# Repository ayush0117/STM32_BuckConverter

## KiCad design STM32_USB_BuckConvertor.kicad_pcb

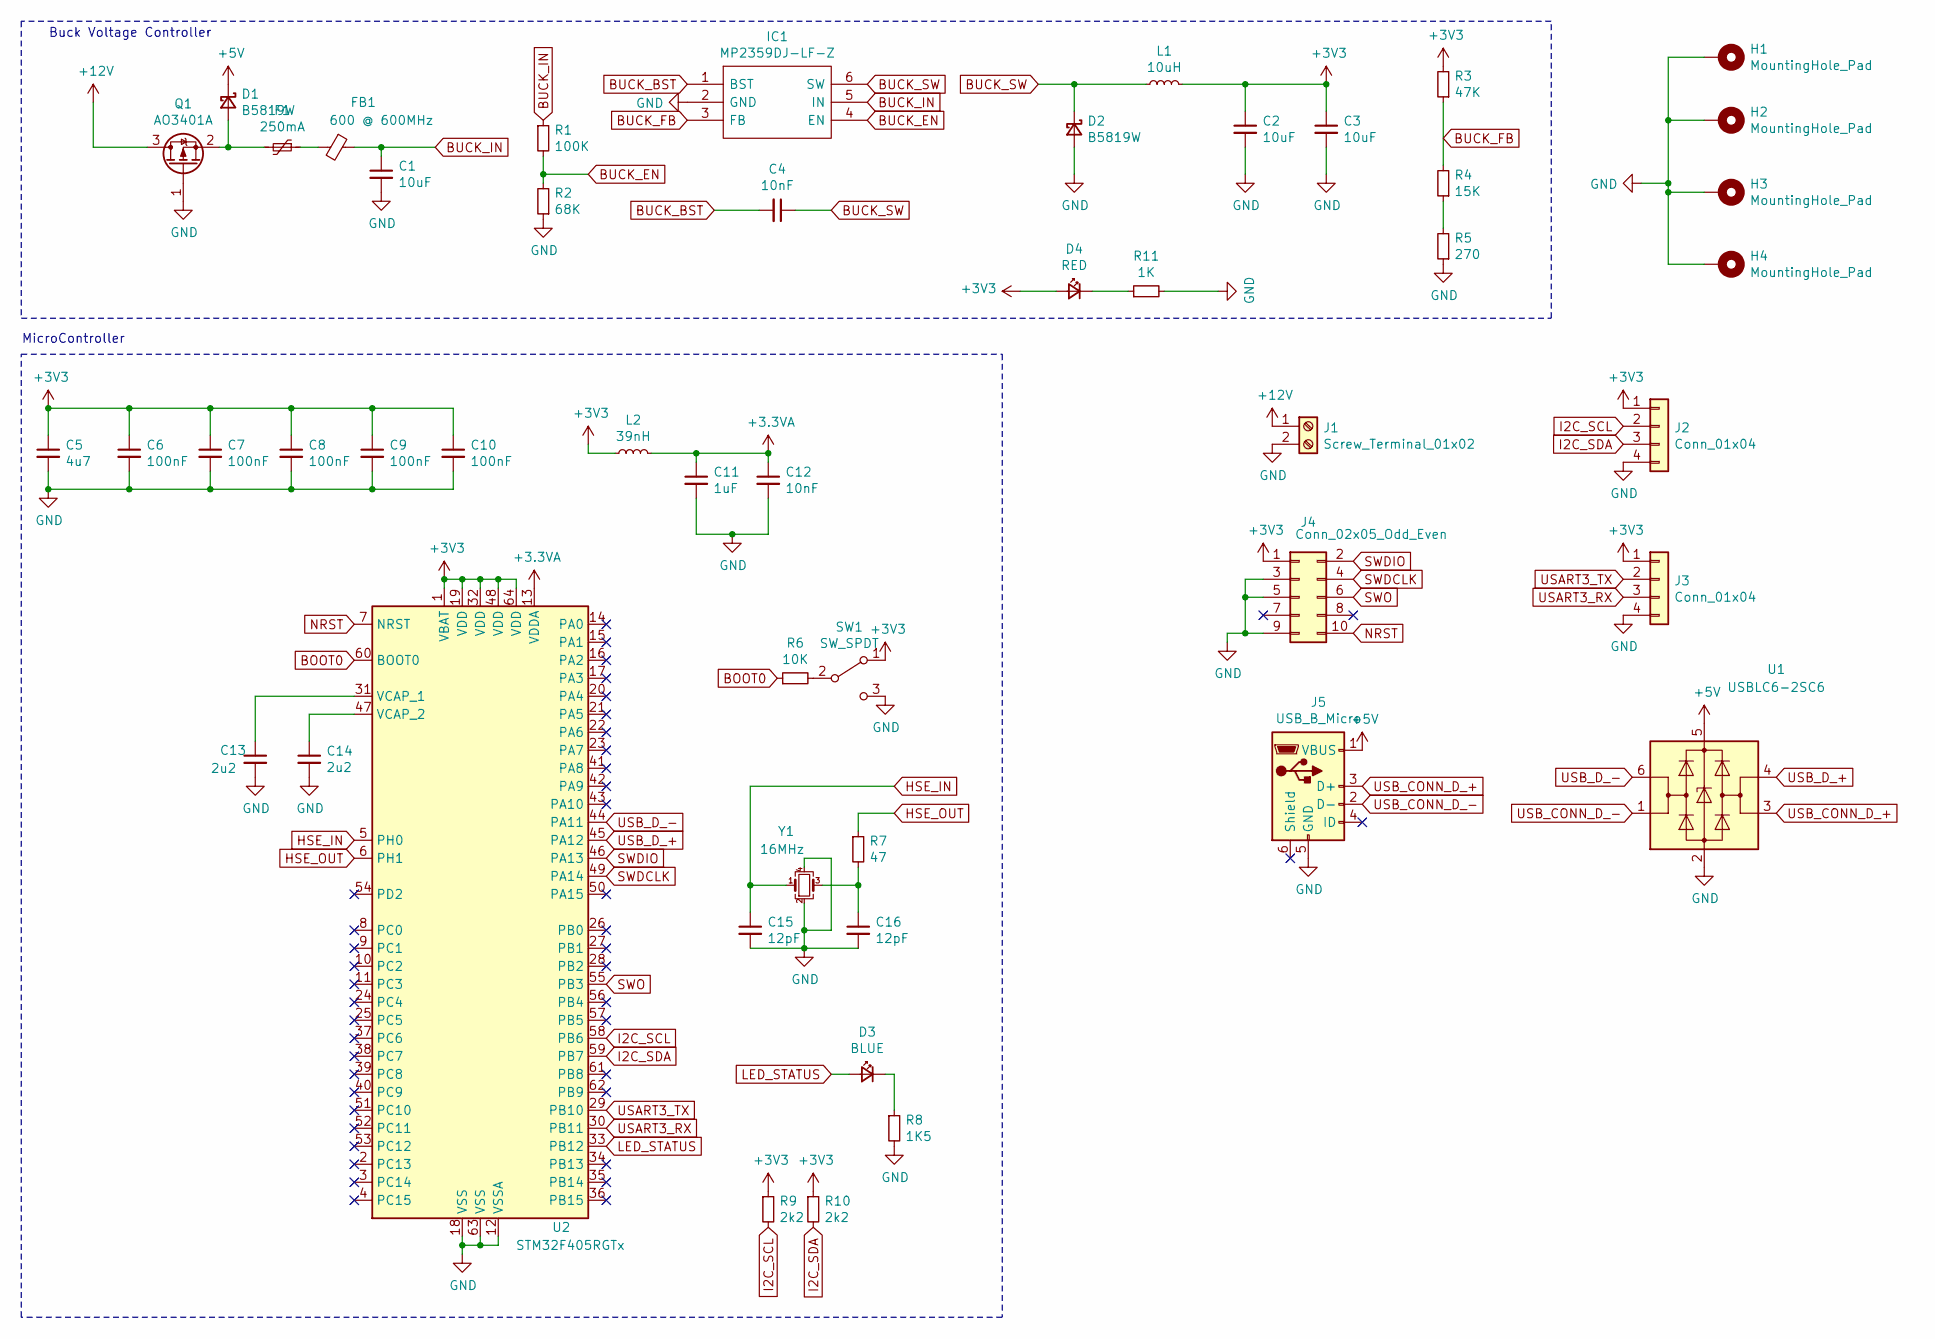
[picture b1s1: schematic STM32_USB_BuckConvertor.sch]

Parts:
C1, C2, C3: 10uF; C_1206_3216Metric
C4, C12: 10nF; C_0402_1005Metric
C5: 4u7; C_0603_1608Metric
C6, C7, C8, C9, C10: 100nF; C_0402_1005Metric
C11: 1uF; C_0402_1005Metric
C13, C14: 2u2; C_0603_1608Metric
C15, C16: 12pF; C_0402_1005Metric
D1, D2: B5819W; D_SOD-123
D3: BLUE; LED_0603_1608Metric
D4: RED; LED_0603_1608Metric
F1: 250mA; Fuse_1206_3216Metric
FB1: 600 @ 600MHz; L_0805_2012Metric
H1, H2, H3, H4: MountingHole_Pad; MountingHole_4.3mm_M4_Pad_Via
IC1: MP2359DJ-LF-Z; SOT-23-6; Manufacturer_Part_Number MP2359DJ-LF-Z; Mouser Part Number 946-MP2359DJLFZ
J1: Screw_Terminal_01x02; TerminalBlock_Phoenix_PT-1,5-2-3.5-H_1x02_P3.50mm_Horizontal
J2, J3: Conn_01x04; Molex_PicoBlade_53048-0410_1x04_P1.25mm_Horizontal
J4: Conn_02x05_Odd_Even; PinSocket_2x05_P1.27mm_Vertical_SMD
J5: USB_B_Micro; USB_Micro-B_Molex-105133-0001
L1: 10uH; L_Sunlord_MWSA0518_5.4x5.2mm
L2: 39nH; L_0402_1005Metric
Q1: AO3401A; SOT-23
R1: 100K; R_0603_1608Metric
R2: 68K; R_0603_1608Metric
R3: 47K; R_0603_1608Metric
R4: 15K; R_0603_1608Metric
R5: 270; R_0603_1608Metric
R6: 10K; R_0402_1005Metric
R7: 47; R_0402_1005Metric
R8: 1K5; R_0603_1608Metric
R9, R10: 2k2; R_0402_1005Metric
R11: 1K; R_0603_1608Metric
SW1: SW_SPDT; SW_SPDT_PCM12
U1: USBLC6-2SC6; SOT-23-6
U2: STM32F405RGTx; LQFP-64_10x10mm_P0.5mm
Y1: 16MHz; Crystal_SMD_3225-4Pin_3.2x2.5mm

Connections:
+3.3VA: C11.1, C12.1, L2.2, U2.13 (VDDA)
+3V3: C2.1, C3.1, C5.1, C6.1, C7.1, C8.1, C9.1, C10.1, D4.2 (A), J2.1, J3.1, J4.1, L1.2, L2.1, R3.2, R9.1, R10.1, SW1.1 (A), U2.1 (VBAT), U2.19 (VDD), U2.32 (VDD), U2.48 (VDD), U2.64 (VDD)
+5V: D1.1 (K), J5.1 (VBUS), U1.5 (VBUS)
+12V: J1.1, Q1.3 (D)
BOOT0: R6.1, U2.60 (BOOT0)
BUCK_BST: C4.2, IC1.1 (BST)
BUCK_EN: IC1.4 (EN), R1.2, R2.2
BUCK_FB: IC1.3 (FB), R3.1, R4.2
BUCK_IN: C1.1, FB1.1, IC1.5 (IN), R1.1
BUCK_SW: C4.1, D2.1 (K), IC1.6 (SW), L1.1
GND: C1.2, C2.2, C3.2, C5.2, C6.2, C7.2, C8.2, C9.2, C10.2, C11.2, C12.2, C13.2, C14.2, C15.2, C16.2, D2.2 (A), H1.1, H2.1, H3.1, H4.1, IC1.2 (GND), J1.2, J2.4, J3.4, J4.3, J4.5, J4.9, J5.5 (GND), Q1.1 (G), R2.1, R5.1, R8.2, R11.2, SW1.3 (C), U1.2 (GND), U2.12 (VSSA), U2.18 (VSS), U2.63 (VSS), Y1.2, Y1.4
HSE_IN: C15.1, U2.5 (PH0), Y1.1
HSE_OUT: R7.1, U2.6 (PH1)
I2C_SCL: J2.2, R9.2, U2.58 (PB6)
I2C_SDA: J2.3, R10.2, U2.59 (PB7)
LED_STATUS: D3.2 (A), U2.33 (PB12)
NRST: J4.10, U2.7 (NRST)
unnamed: C13.1, U2.31 (VCAP_1)
unnamed: C14.1, U2.47 (VCAP_2)
unnamed: C16.1, R7.2, Y1.3
unnamed: D1.2 (A), F1.2, Q1.2 (S)
unnamed: D3.1 (K), R8.1
unnamed: D4.1 (K), R11.1
unnamed: F1.1, FB1.2
unnamed: R4.1, R5.2
unnamed: R6.2, SW1.2 (B)
SWDCLK: J4.4, U2.49 (PA14)
SWDIO: J4.2, U2.46 (PA13)
SWO: J4.6, U2.55 (PB3)
USART3_RX: J3.3, U2.30 (PB11)
USART3_TX: J3.2, U2.29 (PB10)
USB_CONN_D_+: J5.3 (D+), U1.3 (I/O2)
USB_CONN_D_-: J5.2 (D-), U1.1 (I/O1)
USB_D_+: U1.4 (I/O2), U2.45 (PA12)
USB_D_-: U1.6 (I/O1), U2.44 (PA11)

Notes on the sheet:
MicroController
Buck Voltage Controller

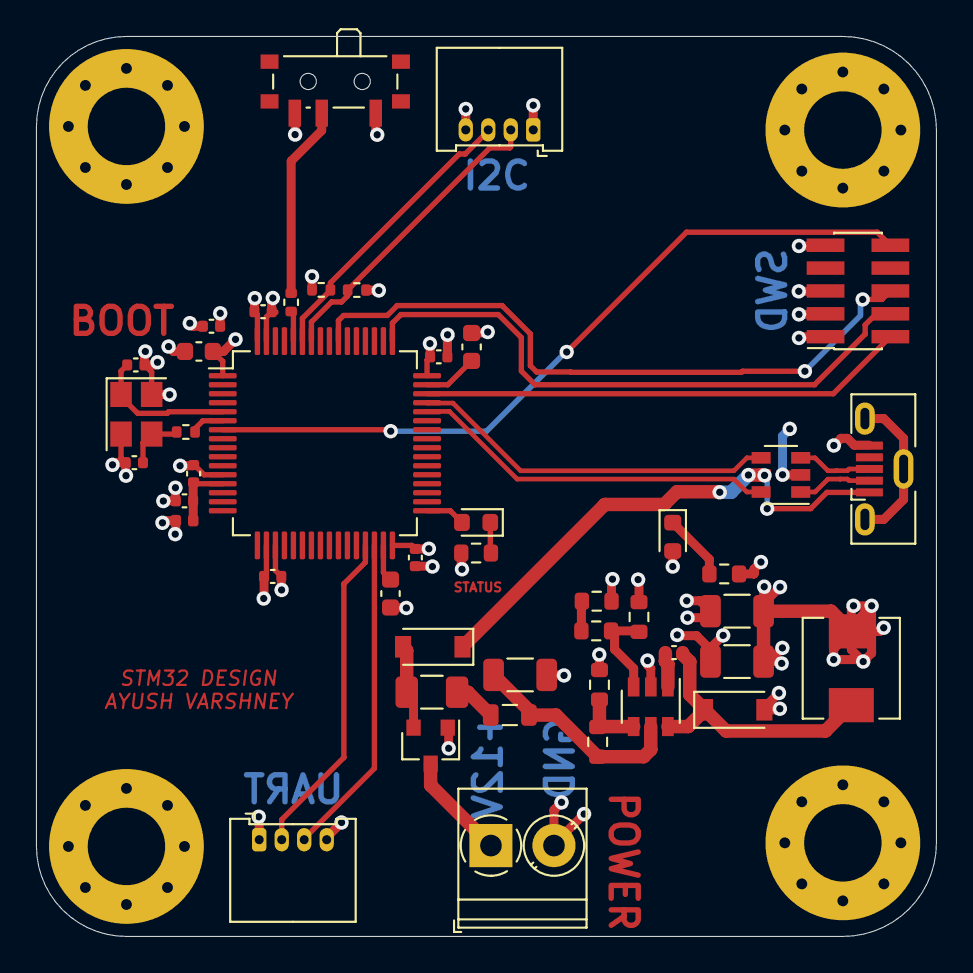
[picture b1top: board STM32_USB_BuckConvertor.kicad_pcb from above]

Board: 4 copper layers, 50.0 x 50.0 mm, 50 parts (0 on the bottom side), 35 nets.

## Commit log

2022-04-28 Create gerber_file
2022-04-28 gerber_file
2022-04-28 Create jhv
2022-04-28 Create bjdcx
